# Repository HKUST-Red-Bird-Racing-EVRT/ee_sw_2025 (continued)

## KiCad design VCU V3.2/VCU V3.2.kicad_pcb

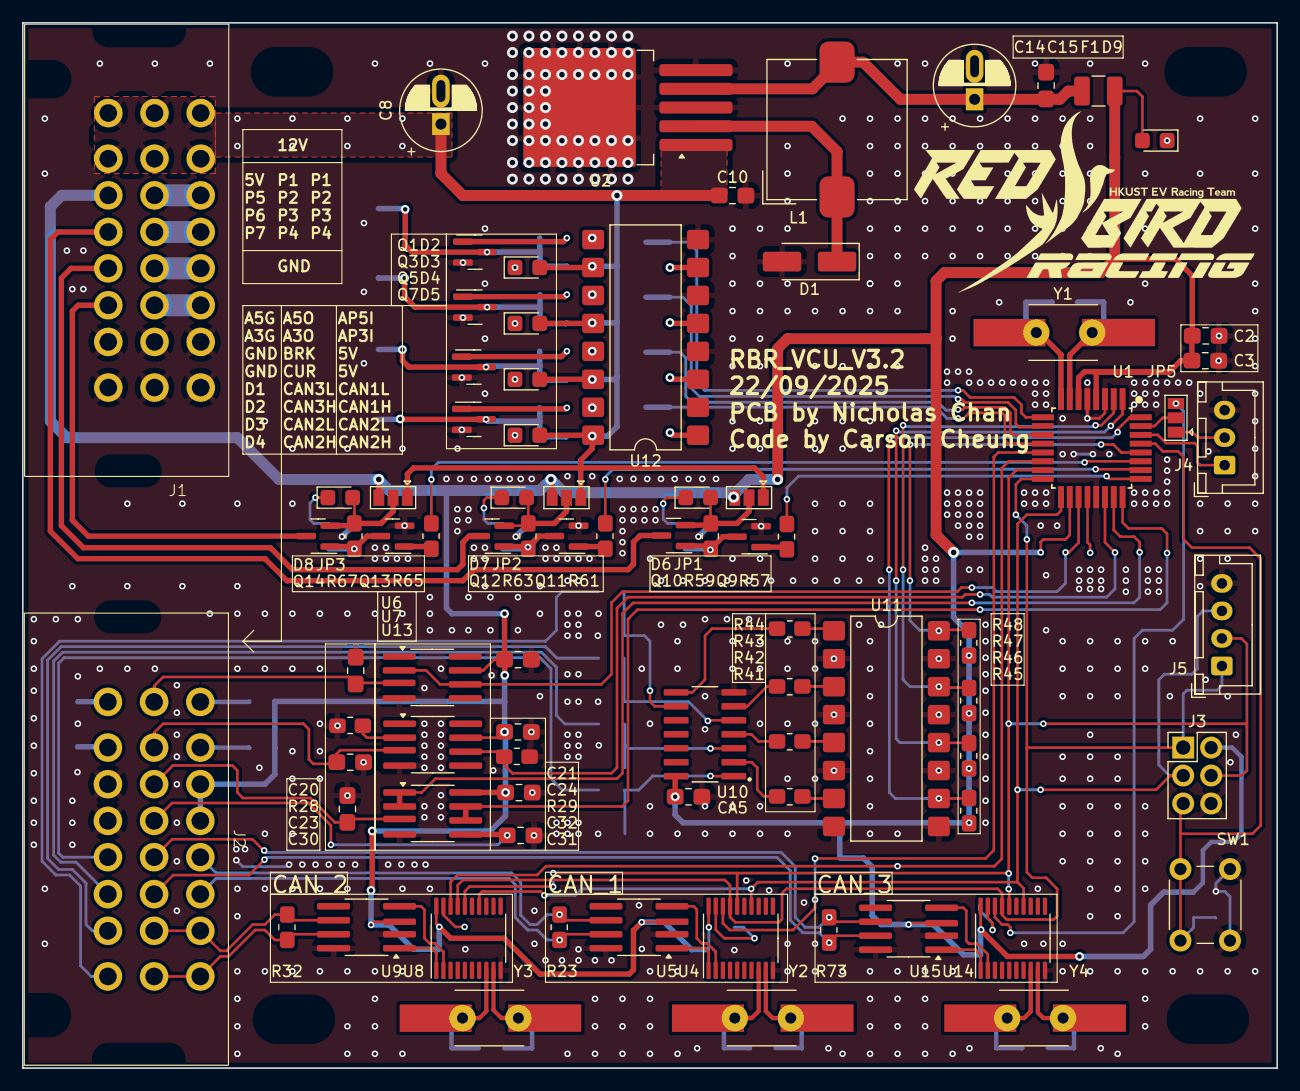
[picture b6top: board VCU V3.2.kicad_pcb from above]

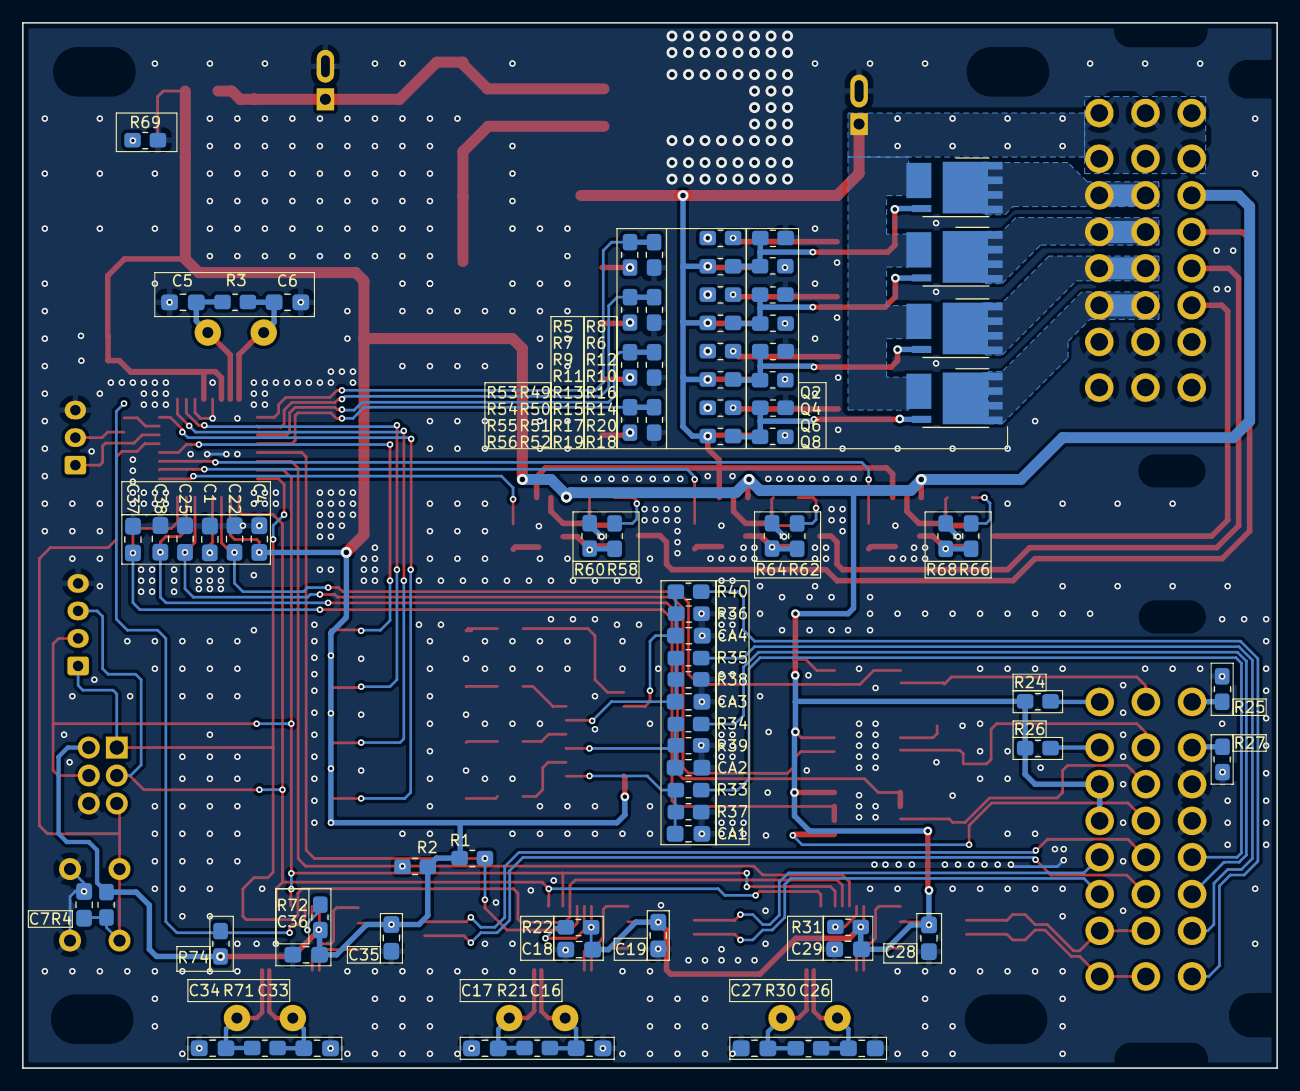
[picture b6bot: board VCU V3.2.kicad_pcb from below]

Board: 2 copper layers, 114.0 x 95.0 mm, 169 parts (83 on the bottom side), 119 nets.

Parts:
C1, C3, C4, C10, C15, C18, C19, C20, C21, C22, C23, C24, C25, C28, C29, C30, C31, C32, C35, C36, C37, C38: 100nF; C_0805_2012Metric_Pad1.18x1.45mm_HandSolder_L
C2, C7: 10uF; C_0805_2012Metric_Pad1.18x1.45mm_HandSolder_L
C5, C6: 20pF; C_0805_2012Metric_Pad1.18x1.45mm_HandSolder_L
C8: 100uF; CP_Radial_D6.3mm_P2.50mm_handsolder
C14: 330uF; CP_Radial_D6.3mm_P2.50mm_handsolder
C16, C17, C26, C27, C33, C34: 16pF; C_0805_2012Metric_Pad1.18x1.45mm_HandSolder_L
CA1, CA2, CA3, CA4, CA5: 100nF; C_0805_2012Metric_Pad1.18x1.45mm_HandSolder_L
D1: SS32; D_SMA_Handsoldering
D2, D3, D4, D5, D6, D7, D8, D9: LED; LED_0805_2012Metric_Pad1.45x1.40mm_HandSolder
F1: 12V 3A; Fuse_1210_3225Metric_Pad1.42x2.65mm_HandSolder
H1, H2, H3, H4: MountingHole_Pad; MountingHole_3.2mmx5mm_M3_ISO7380
J1: HD241_GF30
J2: HD241_24pin
J3: AVR-ISP-6; PinHeader_2x03_P2.54mm_Vertical_handsolder
J4: Conn_01x03; JST_XH_B3B-XH-A_1x03_P2.50mm_Vertical
J5: Conn_01x04; JST_XH_B4B-XH-A_1x04_P2.50mm_Vertical
JP1, JP2, JP3, JP5: Jumper_3_Open; SolderJumper-3_P1.3mm_Open_Pad1.0x1.5mm
L1: 330uH; L_TDK_SLF12575
Q1, Q3, Q5, Q7, Q9, Q11, Q13: MMBT3904; SOT-23
Q2, Q4, Q6, Q8: BSC030P03NS3; Infineon_PG-TDSON-8_6.15x5.15mm
Q10, Q12, Q14: AO3401A; SOT-23
R1, R2, R74: 47k; R_0805_2012Metric_Pad1.20x1.40mm_HandSolder_L
R3, R21, R30, R71: 10M; R_0805_2012Metric_Pad1.20x1.40mm_HandSolder_L
R4: 4k7; R_0805_2012Metric_Pad1.20x1.40mm_HandSolder_L
R5, R6, R7, R9, R10, R11, R13, R14, R15, R17, R18, R19, R29, R33, R34, R35, R40, R41, R42, R43, R44, R53, R54, R55, R56, R57, R58, R59, R61, R62, R63, R65, R66, R67, R69: 1k; R_0805_2012Metric_Pad1.20x1.40mm_HandSolder_L
R8, R12, R16, R20, R60, R64, R68: 100k; R_0805_2012Metric_Pad1.20x1.40mm_HandSolder_L
R22, R31, R36, R37, R38, R39, R72: 10k; R_0805_2012Metric_Pad1.20x1.40mm_HandSolder_L
R23, R32, R73: 120R; R_0805_2012Metric_Pad1.20x1.40mm_HandSolder_L
R24, R25, R26, R27: R; R_0805_2012Metric_Pad1.20x1.40mm_HandSolder_L
R28: 330R; R_0805_2012Metric_Pad1.20x1.40mm_HandSolder_L
R45, R46, R47, R48, R49, R50, R51, R52: 4.7k; R_0805_2012Metric_Pad1.20x1.40mm_HandSolder_L
SW1: SW_Push; SW_PUSH_6mm
U1: ATmega328P-A; TQFP-32_7x7mm_P0.8mm_L
U2: LM2575-5.0BU; TO-263-5_TabPin3_Long
U4, U8, U14: MCP2515-xST; TSSOP-20_4.4x6.5mm_P0.65mm
U5, U9, U15: TJA1051T; SOIC-8_3.9x4.9mm_P1.27mm_RMC_Handsolder
U6, U7: OP07; SOIC-8_3.9x4.9mm_P1.27mm_RMC_Handsolder
U10: 40106; SOIC127P600X175-14N
U11, U12: LTV-847S; SMDIP-16_W9.53mm
U13: SGM722; SOIC-8_3.9x4.9mm_P1.27mm_RMC_Handsolder
Y1: 16MHz; Crystal_HC49-U_Vertical_W_SMD_Handolder
Y2, Y3, Y4: 20MHz; Crystal_HC49-U_Vertical_W_SMD_Handolder

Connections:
+5V: C2.1, C3.1, C4.1, C18.2, C19.2, C21.1, C24.1, C28.2, C29.2, C32.1, C35.2, C36.2, CA5.1, D9.2 (A), F1.1, J1.19, J2.3, J2.4, J3.2 (VCC), JP1.3 (B), JP2.3 (B), JP3.3 (B), R1.1, R2.1, R4.1, R22.2, R24.1, R26.1, R31.2, R45.2, R46.2, R47.2, R48.2, R72.2, R74.1, U1.4 (VCC), U1.6 (VCC), U1.18 (AVCC), U4.20 (VDD), U5.3 (VCC), U6.7 (V+), U7.7 (V+), U8.20 (VDD), U9.3 (VCC), U10.14 (VDD), U13.8 (V+), U14.20 (VDD), U15.3 (VCC)
+12V: C8.1, C10.1, D2.2 (A), D3.2 (A), D4.2 (A), D5.2 (A), J1.1, J1.2, J1.9, J1.10, J1.17, J1.18, JP1.1 (A), JP2.1 (A), JP3.1 (A), Q2.1 (S), Q2.2 (S), Q2.3 (S), Q4.1 (S), Q4.2 (S), Q4.3 (S), Q6.1 (S), Q6.2 (S), Q6.3 (S), Q8.1 (S), Q8.2 (S), Q8.3 (S), R7.1, R11.1, R15.1, R19.1, U2.1 (VIN), U12.10, U12.12, U12.14, U12.16
/CAN BUS_1/XTAL1: C17.1, R21.1, U4.9 (OSC1), Y2.2
/CAN BUS_1/XTAL2: C16.1, R21.2, U4.8 (OSC2), Y2.1
/CAN BUS_2/XTAL1: C27.1, R30.1, U8.9 (OSC1), Y3.2
/CAN BUS_2/XTAL2: C26.1, R30.2, U8.8 (OSC2), Y3.1
/CAN BUS_3/XTAL1: C34.1, R71.1, U14.9 (OSC1), Y4.2
/CAN BUS_3/XTAL2: C33.1, R71.2, U14.8 (OSC2), Y4.1
/PDU_P4_1/PDU_1/MOS_GATE: Q1.3 (C), Q2.4 (G), R6.2, R7.2, R8.1
/PDU_P4_1/PDU_1/SIGNAL: R5.1, U12.9
/PDU_P4_1/PDU_2/MOS_GATE: Q3.3 (C), Q4.4 (G), R10.2, R11.2, R12.1
/PDU_P4_1/PDU_2/SIGNAL: R9.1, U12.11
/PDU_P4_1/PDU_3/MOS_GATE: Q5.3 (C), Q6.4 (G), R14.2, R15.2, R16.1
/PDU_P4_1/PDU_3/SIGNAL: R13.1, U12.13
/PDU_P4_1/PDU_4/MOS_GATE: Q7.3 (C), Q8.4 (G), R18.2, R19.2, R20.1
/PDU_P4_1/PDU_4/SIGNAL: R17.1, U12.15
APPS_3V3: C25.1, R29.2, U1.22 (ADC7), U7.6
APPS_3VGND: J2.18, R27.1
APPS_3VIN: J2.2, R26.2
APPS_3VOUT: C23.1, J2.10, U7.3 (+)
APPS_5V: C22.1, U1.19 (ADC6), U6.2 (-), U6.6
APPS_5VGND: J2.17, R25.1
APPS_5VIN: J2.1, R24.2
APPS_5VOUT: C20.1, J2.9, U6.3 (+)
BRAKE_AIN: C30.1, J2.11, U13.3 (+)
BRAKE_AIN_MCU: C38.2, U1.23 (PC0), U13.1, U13.2 (-)
CAN1+: J2.6, R23.2, U5.7 (CANH)
CAN1-: J2.5, R23.1, U5.6 (CANL)
CAN2+: J2.8, J2.16, R32.2, U9.7 (CANH)
CAN2-: J2.7, J2.15, R32.1, U9.6 (CANL)
CAN3+: J2.14, R73.2, U15.7 (CANH)
CAN3-: J2.13, R73.1, U15.6 (CANL)
CS_1: R1.2, U1.13 (PB1), U4.18 (~CS)
CS_2: R2.2, U1.14 (PB2), U8.18 (~CS)
CS_3: JP5.3 (B), R74.2, U14.18 (~CS)
CURRENT_AIN: C31.1, J2.12, U13.5 (+)
CURRENT_MCU: C37.2, U1.24 (PC1), U13.6 (-), U13.7
DIN5V_1: R45.1, U1.32 (PD2), U11.10
DIN5V_2: R46.1, U1.1 (PD3), U11.12
DIN5V_3: R47.1, U1.2 (PD4), U11.14
DIN_1: J2.21, R33.1
DIN_2: J2.22, R34.1
DIN_3: J2.23, R35.1
GND: C1.2, C2.2, C3.2, C4.2, C5.2, C6.2, C7.2, C8.2, C10.2, C14.2, C15.2, C16.2, C17.2, C18.1, C19.1, C20.2, C21.2, C22.2, C23.2, C24.2, C25.2, C26.2, C27.2, C28.1, C29.1, C30.2, C31.2, C32.2, C33.2, C34.2, C35.1, C36.1, C37.1, C38.1, CA1.1, CA2.2, CA3.2, CA4.2, CA5.2, D1.2 (A), J1.7, J1.8, J1.15, J1.16, J1.23, J1.24, J2.19, J2.20, J3.6 (GND), J4.3, J5.4, Q1.2 (E), Q3.2 (E), Q5.2 (E), Q7.2 (E), Q9.2 (E), Q11.2 (E), Q13.2 (E), R8.2, R12.2, R16.2, R20.2, R25.2, R27.2, R28.2, R29.1, R36.2, R37.1, R38.2, R39.2, R49.1, R50.1, R51.1, R52.1, R60.2, R64.2, R68.2, R69.2, SW1.1, U1.3 (GND), U1.5 (GND), U1.21 (GND), U2.3 (GND), U2.5 (~ON/OFF), U4.10 (VSS), U5.2 (GND), U5.8 (S), U6.4 (V-), U7.4 (V-), U8.10 (VSS), U9.2 (GND), U9.8 (S), U10.7 (VSS), U11.2, U11.4, U11.6, U11.8, U11.9, U11.11, U11.13, U11.15, U12.2, U12.4, U12.6, U12.8, U13.4 (V-), U14.10 (VSS), U15.2 (GND), U15.8 (S)
IGN_5V: R48.1, U1.28 (PC5), U11.16
IGN_12V: J2.24, R40.1
MISO: J3.1 (MISO), J5.1, U1.16 (PB4), U4.17 (SO), U8.17 (SO), U14.17 (SO)
MOSI: J3.4 (MOSI), J5.2, U1.15 (PB3), U4.16 (SI), U8.16 (SI), U14.16 (SI)
unnamed: CA1.2, R33.2, R37.2, U10.1
unnamed: CA2.1, R34.2, R39.1, U10.3
unnamed: CA3.1, R35.2, R38.1, U10.5
unnamed: CA4.1, R36.1, R40.2, U10.9
unnamed: D1.1 (K), L1.1, U2.2 (OUT)
unnamed: D2.1 (K), R6.1
unnamed: D3.1 (K), R10.1
unnamed: D4.1 (K), R14.1
unnamed: D5.1 (K), R18.1
unnamed: D6.2 (A), JP1.2 (C), Q10.2 (S), R59.1
unnamed: D6.1 (K), R58.1
unnamed: D7.2 (A), JP2.2 (C), Q12.2 (S), R63.1
unnamed: D7.1 (K), R62.1
unnamed: D8.2 (A), JP3.2 (C), Q14.2 (S), R67.1
unnamed: D8.1 (K), R66.1
unnamed: D9.1 (K), R69.1
unnamed: JP5.2 (C), U1.31 (PD1)
unnamed: Q1.1 (B), R5.2
unnamed: Q3.1 (B), R9.2
unnamed: Q5.1 (B), R13.2
unnamed: Q7.1 (B), R17.2
unnamed: Q9.1 (B), R57.2
unnamed: Q9.3 (C), Q10.1 (G), R58.2, R59.2, R60.1
unnamed: Q11.1 (B), R61.2
unnamed: Q11.3 (C), Q12.1 (G), R62.2, R63.2, R64.1
unnamed: Q13.1 (B), R65.2
unnamed: Q13.3 (C), Q14.1 (G), R66.2, R67.2, R68.1
unnamed: R41.1, U10.2
unnamed: R41.2, U11.7
unnamed: R42.1, U10.4
unnamed: R42.2, U11.5
unnamed: R43.1, U10.6
unnamed: R43.2, U11.3
unnamed: R44.1, U10.8
unnamed: R44.2, U11.1
unnamed: R53.2, U12.7
unnamed: R54.2, U12.5
unnamed: R55.2, U12.3
unnamed: R56.2, U12.1
unnamed: C1.1, U1.20 (AREF)
unnamed: C14.1, C15.1, F1.2, L1.2, U2.4 (FB)
unnamed: U4.2 (RXCAN), U5.4 (RXD)
unnamed: U4.1 (TXCAN), U5.1 (TXD)
unnamed: R22.1, U4.19 (~RESET)
unnamed: R28.1, U7.2 (-)
unnamed: U8.2 (RXCAN), U9.4 (RXD)
unnamed: U8.1 (TXCAN), U9.1 (TXD)
unnamed: R31.1, U8.19 (~RESET)
unnamed: U14.2 (RXCAN), U15.4 (RXD)
unnamed: U14.1 (TXCAN), U15.1 (TXD)
unnamed: R72.1, U14.19 (~RESET)
OUT_1: R49.2, R53.1, U1.9 (PD5)
OUT_2: R50.2, R54.1, U1.10 (PD6)
OUT_3: R51.2, R55.1, U1.11 (PD7)
OUT_4: R52.2, R56.1, U1.12 (PB0)
OUT_5: R57.1, U1.25 (PC2)
OUT_6: R61.1, U1.26 (PC3)
OUT_7: R65.1, U1.27 (PC4)
PDU_1: J1.3, J1.11, Q2.5 (D)
PDU_2: J1.4, J1.12, Q4.5 (D)
PDU_3: J1.5, J1.13, Q6.5 (D)
PDU_4: J1.6, J1.14, Q8.5 (D)
PDU_5: J1.20, Q10.3 (D)
PDU_6: J1.21, Q12.3 (D)
PDU_7: J1.22, Q14.3 (D)
RESET: C7.1, J3.5 (~RST), R4.2, SW1.2, U1.29 (~RESET/PC6)
RXD: J4.1, U1.30 (PD0)
SCK: J3.3 (SCK), J5.3, U1.17 (PB5), U4.14 (SCK), U8.14 (SCK), U14.14 (SCK)
TXD: J4.2, JP5.1 (A)
XTAL1: C5.1, R3.1, U1.7 (XTAL1/PB6), Y1.2
XTAL2: C6.1, R3.2, U1.8 (XTAL2/PB7), Y1.1

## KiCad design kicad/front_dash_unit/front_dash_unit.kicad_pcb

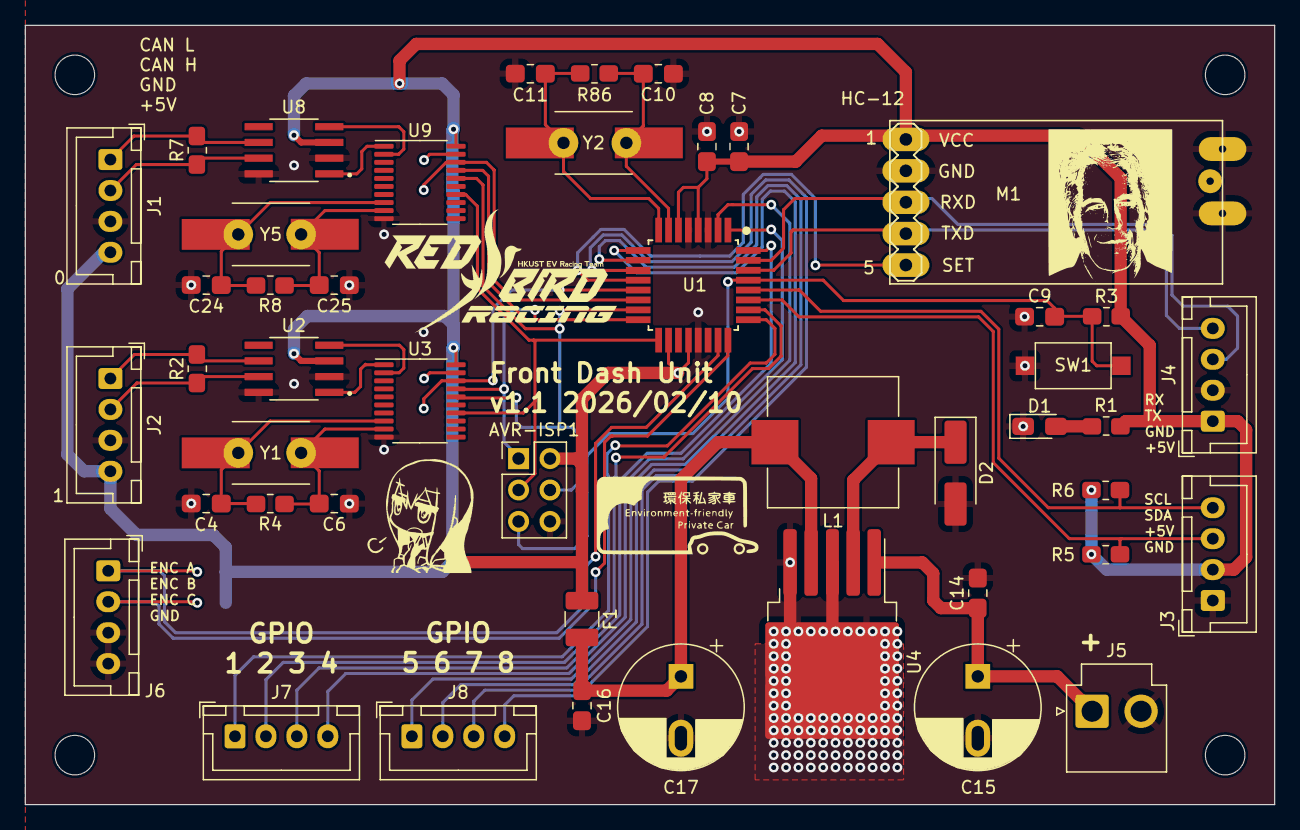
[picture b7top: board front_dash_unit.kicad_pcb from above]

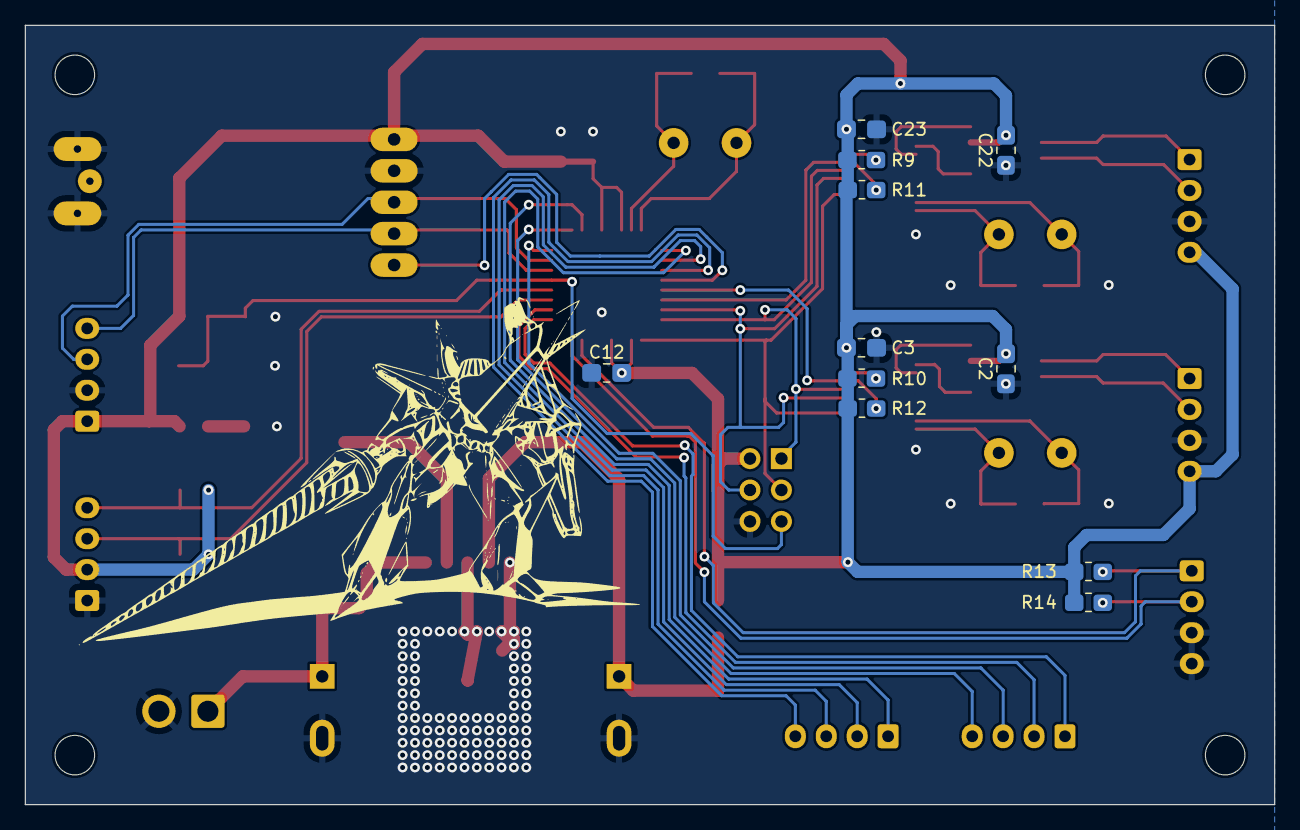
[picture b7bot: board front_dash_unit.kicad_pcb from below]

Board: 2 copper layers, 101.0 x 63.0 mm, 62 parts (11 on the bottom side), 43 nets.

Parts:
AVR-ISP1: Conn_02x03_Odd_Even; PinHeader_2x03_P2.54mm_Vertical
C2, C3, C7, C8, C14, C16, C22, C23: 100nF; C_0805_2012Metric_Pad1.18x1.45mm_HandSolder_L
C4, C6, C10, C11, C24, C25: 22pF; C_0805_2012Metric_Pad1.18x1.45mm_HandSolder_L
C9, C12: 10uF; C_0805_2012Metric_Pad1.18x1.45mm_HandSolder_L
C15, C17: 330uF; CP_Radial_D10.0mm_P5.00mm_F
D1: LED; LED_0805_2012Metric_Pad1.15x1.40mm_HandSolder
D2: 1N5819; D_SMA_Handsoldering
F1: Fuse; Fuse_1210_3225Metric_Pad1.42x2.65mm_HandSolder
G0: LOGO
H1, H2, H3, H4: MountingHole; MountingHole_3.2mm_M3
J1, J2, J3, J4, J6, J7, J8: Conn_01x04_Socket; JST_XH_B4B-XH-A_1x04_P2.50mm_Vertical
J5: Conn_01x02_Socket; JST_VH_B2P-VH-B_1x02_P3.96mm_Vertical
L1: 330uH; L_10.4x10.4_H4.8
M1: HC-12; MA05-1
R1: 1k; R_0805_2012Metric_Pad1.20x1.40mm_HandSolder_L
R2, R7: 120; R_0805_2012Metric_Pad1.20x1.40mm_HandSolder_L
R3, R5, R6, R13, R14: 4.7k; R_0805_2012Metric_Pad1.20x1.40mm_HandSolder_L
R4, R8, R86: 10M; R_0805_2012Metric_Pad1.20x1.40mm_HandSolder_L
R9, R10, R11, R12: 10k; R_0805_2012Metric_Pad1.20x1.40mm_HandSolder_L
SW1: SW_Push; SW_SPST_CK_RS282G05A3
U1: ATmega328-A; TQFP-32_7x7mm_P0.8mm_L
U2, U8: TJA1050T_CM_118; SOIC127P600X175-8N
U3, U9: MCP2515-xST; TSSOP-20_4.4x6.5mm_P0.65mm
U4: LM2575-5.0BU; TO-263-5_TabPin3
Y1, Y2, Y5: 20MHz; Crystal_HC49-U_Vertical_W_SMD

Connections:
+5V: AVR-ISP1.2, C2.2, C3.2, C7.2, C8.2, C12.2, C22.2, C23.2, F1.1, J1.4, J2.4, J3.2, J4.1, M1.1 (VCC), R1.1, R3.2, R5.1, R6.1, R9.2, R10.2, R11.2, R12.2, R13.2, R14.2, U1.4 (VCC), U1.6 (VCC), U1.18 (AVCC), U1.20 (AREF), U2.3 (VCC), U3.20 (VDD), U8.3 (VCC), U9.20 (VDD)
+12V: C14.1, C15.1, J5.1, U4.1 (VIN)
/CAN0/CAN_RX: U8.4 (RXD), U9.2 (RXCAN)
/CAN0/CAN_TX: U8.1 (TXD), U9.1 (TXCAN)
/CAN1/CAN_RX: U2.4 (RXD), U3.2 (RXCAN)
/CAN1/CAN_TX: U2.1 (TXD), U3.1 (TXCAN)
CAN0H: J1.2, R7.1, U8.7 (CANH)
CAN0L: J1.1, R7.2, U8.6 (CANL)
CAN0_CS: R11.1, U1.14 (PB2), U9.18 (~CS)
CAN1H: J2.2, R2.1, U2.7 (CANH)
CAN1L: J2.1, R2.2, U2.6 (CANL)
CAN1_CS: R12.1, U1.13 (PB1), U3.18 (~CS)
ENC_A: J6.1, R13.1, U1.23 (PC0)
ENC_B: J6.2, R14.1, U1.24 (PC1)
GND: AVR-ISP1.6, C2.1, C3.1, C4.1, C6.1, C7.1, C8.1, C9.1, C10.1, C11.1, C12.1, C14.2, C15.2, C16.2, C17.2, C22.1, C23.1, C24.1, C25.1, D1.1 (K), D2.2 (A), J1.3, J2.3, J3.1, J4.2, J5.2, J6.3, J6.4, M1.2 (GND), M1.GND (GND1), M1.GND1, SW1.1, U1.3 (GND), U1.5 (GND), U1.21 (GND), U2.2 (GND), U2.8 (S), U3.10 (VSS), U4.3 (GND), U4.5 (~ON/OFF), U8.2 (GND), U8.8 (S), U9.10 (VSS)
GPIO_1: J7.1, U1.25 (PC2)
GPIO_2: J7.2, U1.26 (PC3)
GPIO_3: J7.3, U1.32 (PD2)
GPIO_4: J7.4, U1.1 (PD3)
GPIO_5: J8.1, U1.2 (PD4)
GPIO_6: J8.2, U1.9 (PD5)
GPIO_7: J8.3, U1.10 (PD6)
GPIO_8: J8.4, U1.11 (PD7)
HC12_SET: M1.5 (SET), U1.12 (PB0)
MISO: AVR-ISP1.1, U1.16 (PB4), U3.17 (SO), U9.17 (SO)
MOSI: AVR-ISP1.4, U1.15 (PB3), U3.16 (SI), U9.16 (SI)
unnamed: D1.2 (A), R1.2
unnamed: D2.1 (K), L1.1, U4.2 (OUT)
unnamed: C6.2, R4.1, U3.9 (OSC1), Y1.1
unnamed: C4.2, R4.2, U3.8 (OSC2), Y1.2
unnamed: R10.1, U3.19 (~RESET)
unnamed: C16.1, C17.1, F1.2, L1.2, U4.4 (FB)
unnamed: C25.2, R8.1, U9.9 (OSC1), Y5.1
unnamed: C24.2, R8.2, U9.8 (OSC2), Y5.2
unnamed: R9.1, U9.19 (~RESET)
RST: AVR-ISP1.5, C9.2, R3.1, SW1.2, U1.29 (~RESET/PC6)
RXD: J4.4, M1.4 (TXD), U1.30 (PD0)
SCK: AVR-ISP1.3, U1.17 (PB5), U3.14 (SCK), U9.14 (SCK)
SCL: J3.4, R6.2, U1.28 (PC5)
SDA: J3.3, R5.2, U1.27 (PC4)
TXD: J4.3, M1.3 (RXD), U1.31 (PD1)
XTAL1: C10.2, R86.2, U1.7 (XTAL1/PB6), Y2.2
XTAL2: C11.2, R86.1, U1.8 (XTAL2/PB7), Y2.1

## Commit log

2026-02-13 front dash from Marco
2026-02-19 what
2026-03-31 pudh
2026-05-20 file structure
2026-05-20 Test Upload
